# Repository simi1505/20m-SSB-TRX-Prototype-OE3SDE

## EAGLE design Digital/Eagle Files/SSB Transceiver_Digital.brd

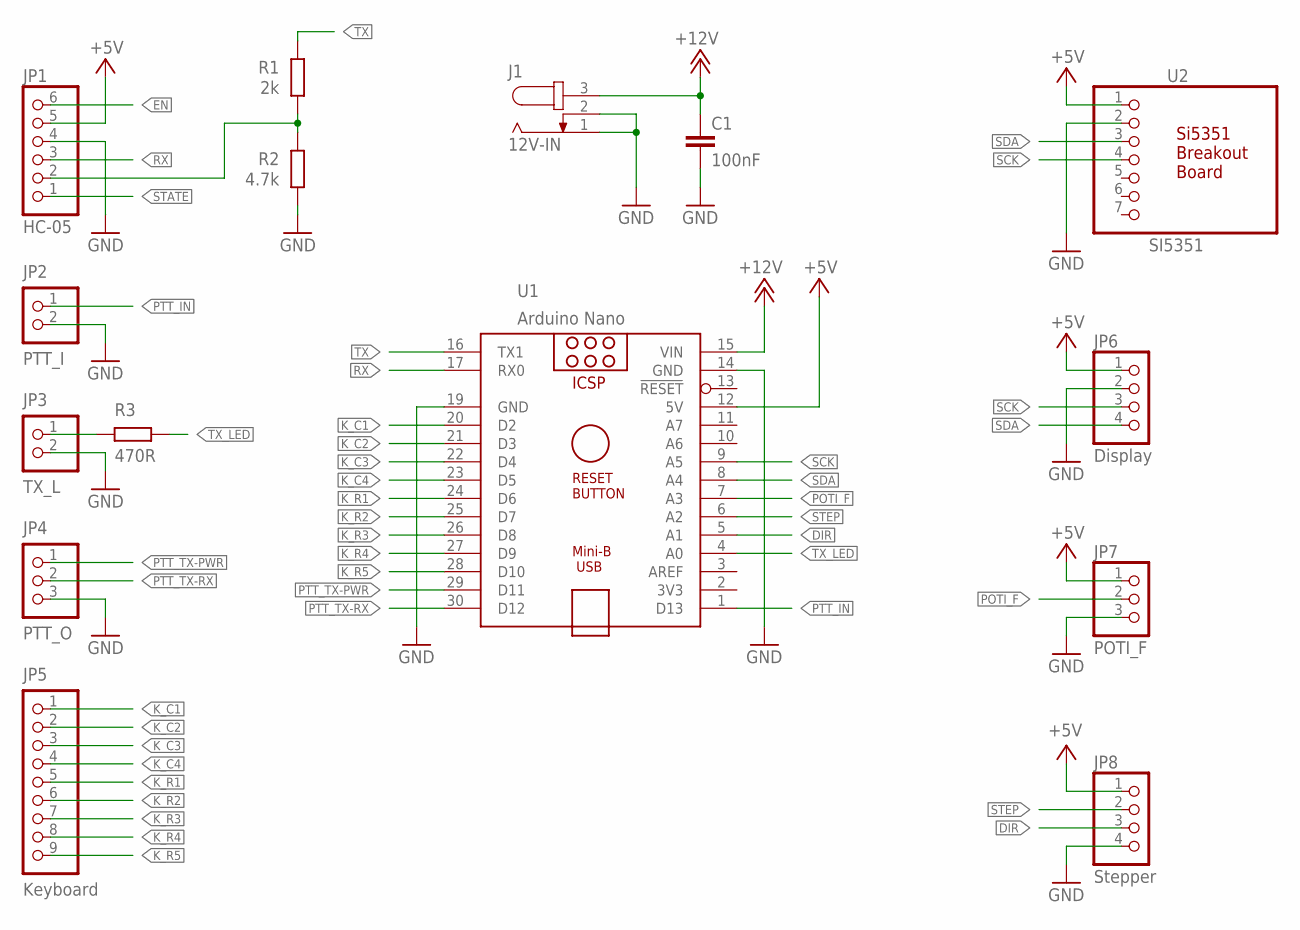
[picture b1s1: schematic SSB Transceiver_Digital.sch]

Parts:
C1: 100nF; C0805K
J1: 12V-IN; SPC4078
JP1: HC-05; 1X06
JP2: PTT_I; 1X02
JP3: TX_L; 1X02
JP4: PTT_O; 1X03
JP5: Keyboard; 1X09
JP6: Display; 1X04
JP7: POTI_F; 1X03
JP8: Stepper; 1X04
R1: 2k; R0805
R2: 4.7k; R0805
R3: 470R; R0805
U1: Arduino Nano; ARDUINO_NANO
U2: SI5351; 1X07

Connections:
+5V: JP1.5, JP6.1, JP7.1, JP8.1, U1.12 (5V), U2.1
+12V: C1.1, J1.3, U1.15 (VIN)
DIR: JP8.3, U1.5 (A1)
EN: JP1.6
GND: C1.2, J1.1, J1.2, JP1.4, JP2.2, JP3.2, JP4.3, JP6.2, JP7.3, JP8.4, R2.1, U1.14 (GND), U1.19 (GND), U2.2
K_C1: JP5.1, U1.20 (D2)
K_C2: JP5.2, U1.21 (D3)
K_C3: JP5.3, U1.22 (D4)
K_C4: JP5.4, U1.23 (D5)
K_R1: JP5.5, U1.24 (D6)
K_R2: JP5.6, U1.25 (D7)
K_R3: JP5.7, U1.26 (D8)
K_R4: JP5.8, U1.27 (D9)
K_R5: JP5.9, U1.28 (D10)
unnamed: JP3.1, R3.2
unnamed: JP1.2, R1.1, R2.2
POTI_F: JP7.2, U1.7 (A3)
PTT_IN: JP2.1, U1.1 (D13)
PTT_TX-PWR: JP4.1, U1.29 (D11)
PTT_TX-RX: JP4.2, U1.30 (D12)
RX: JP1.3, U1.17 (RX0)
SCK: JP6.3, U1.9 (A5), U2.4
SDA: JP6.4, U1.8 (A4), U2.3
STATE: JP1.1
STEP: JP8.2, U1.6 (A2)
TX: R1.2, U1.16 (TX1)
TX_LED: R3.1, U1.4 (A0)

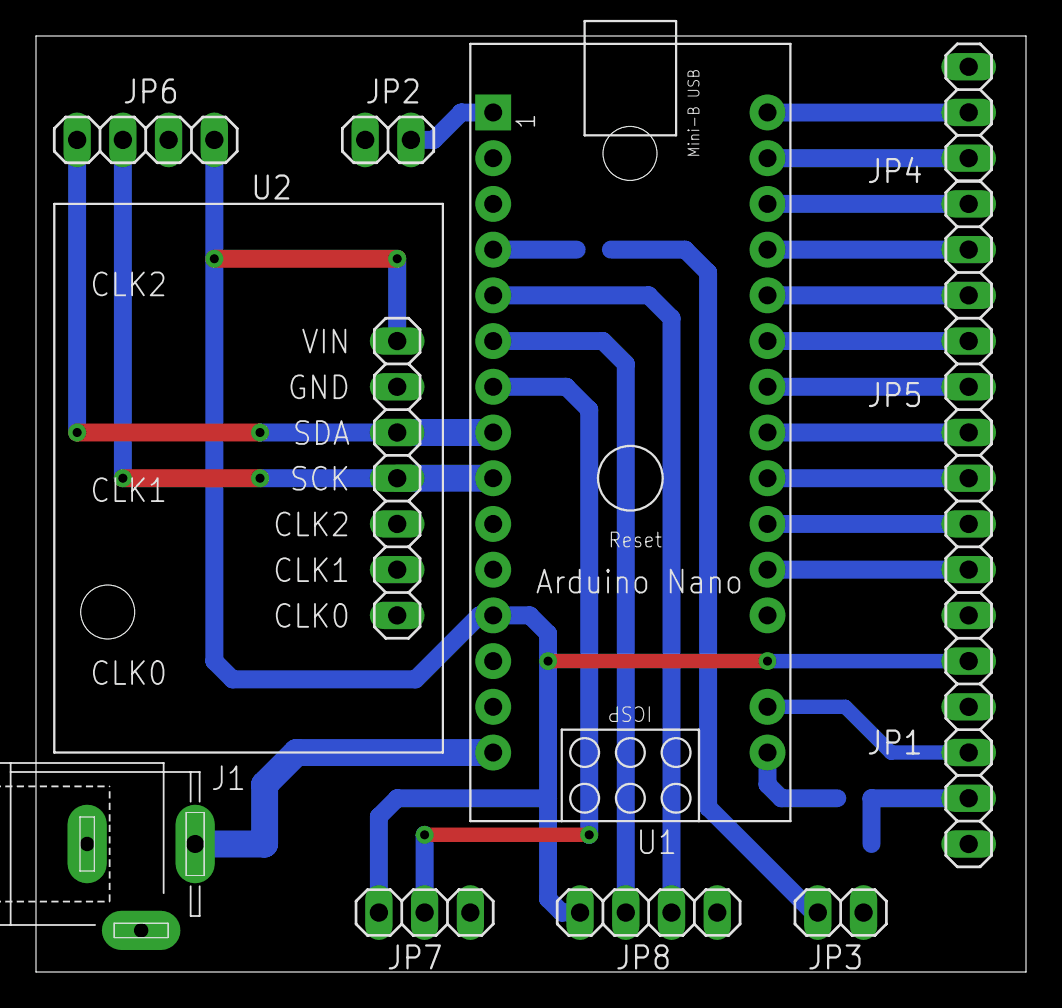
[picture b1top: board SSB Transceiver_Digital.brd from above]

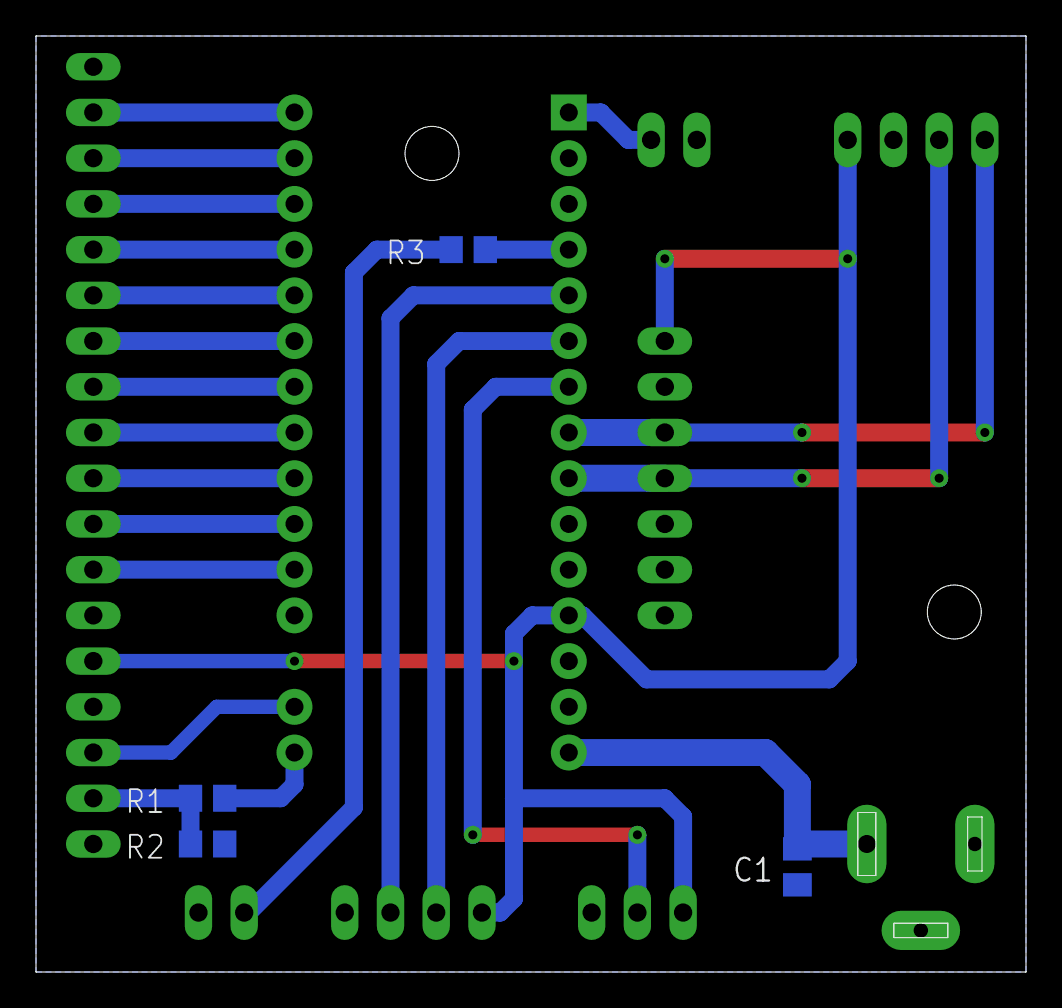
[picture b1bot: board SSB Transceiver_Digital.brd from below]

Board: 2 copper layers, 55.0 x 52.0 mm, 15 parts (4 on the bottom side), 25 nets.

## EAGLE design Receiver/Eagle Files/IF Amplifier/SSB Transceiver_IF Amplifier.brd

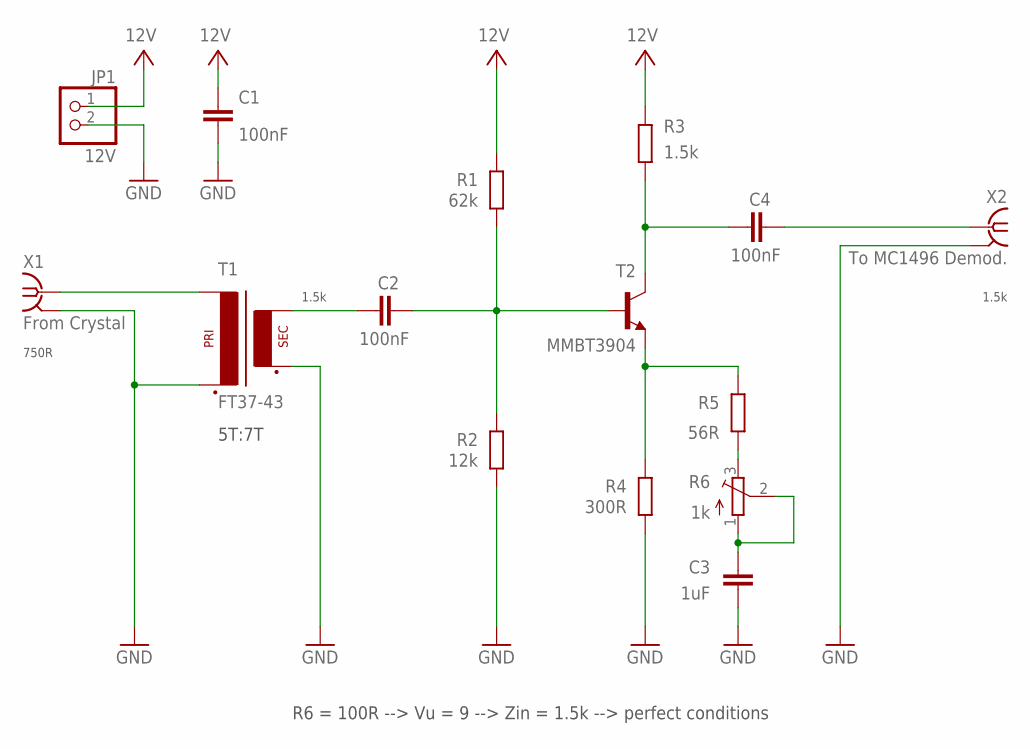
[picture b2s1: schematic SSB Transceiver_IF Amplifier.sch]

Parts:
C1, C2, C4: 100nF; C0805
C3: 1uF; C0805
JP1: 12V; 1X02
R1: 62k; R0805
R2: 12k; R0805
R3: 1.5k; R0805
R4: 300R; R0805
R5: 56R; R0805
R6: 1k; 3223G
T1: FT37-43; FT37-43SMD
T2: MMBT3904; SOT23-BEC
X1: From Crystal; J502-ND-142-0711-821/826
X2: To MC1496 Demod.; J502-ND-142-0711-821/826

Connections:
GND: C1.1, C3.1, JP1.2, R2.2, R4.2, T1.P$2 (P2), T1.S$2 (S2), X1.G@1 (2), X1.G@2 (2), X1.G@3 (2), X1.G@4 (2), X2.G@1 (2), X2.G@2 (2), X2.G@3 (2), X2.G@4 (2)
unnamed: R4.1, R5.1, T2.E
unnamed: C3.2, R6.1 (A), R6.2 (S)
unnamed: C4.1, R3.2, T2.C
unnamed: T1.P$1 (P1), X1.1
unnamed: C2.2, R1.2, R2.1, T2.B
unnamed: C4.2, X2.1
unnamed: C2.1, T1.S$1 (S1)
unnamed: R5.2, R6.3 (E)
VCC: C1.2, JP1.1, R1.1, R3.1

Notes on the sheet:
750R
1.5k
5T:7T
R6 = 100R --> Vu = 9 --> Zin = 1.5k --> perfect conditions

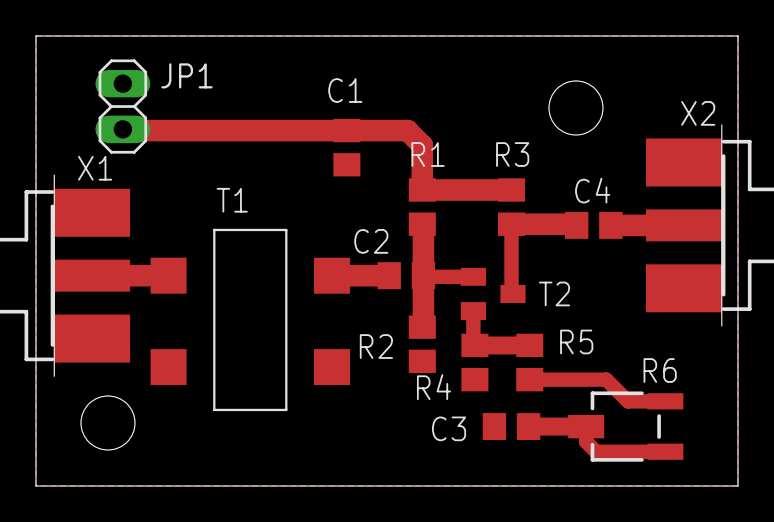
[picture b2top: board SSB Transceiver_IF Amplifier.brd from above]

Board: 2 copper layers, 39.0 x 25.0 mm, 15 parts (0 on the bottom side), 10 nets.

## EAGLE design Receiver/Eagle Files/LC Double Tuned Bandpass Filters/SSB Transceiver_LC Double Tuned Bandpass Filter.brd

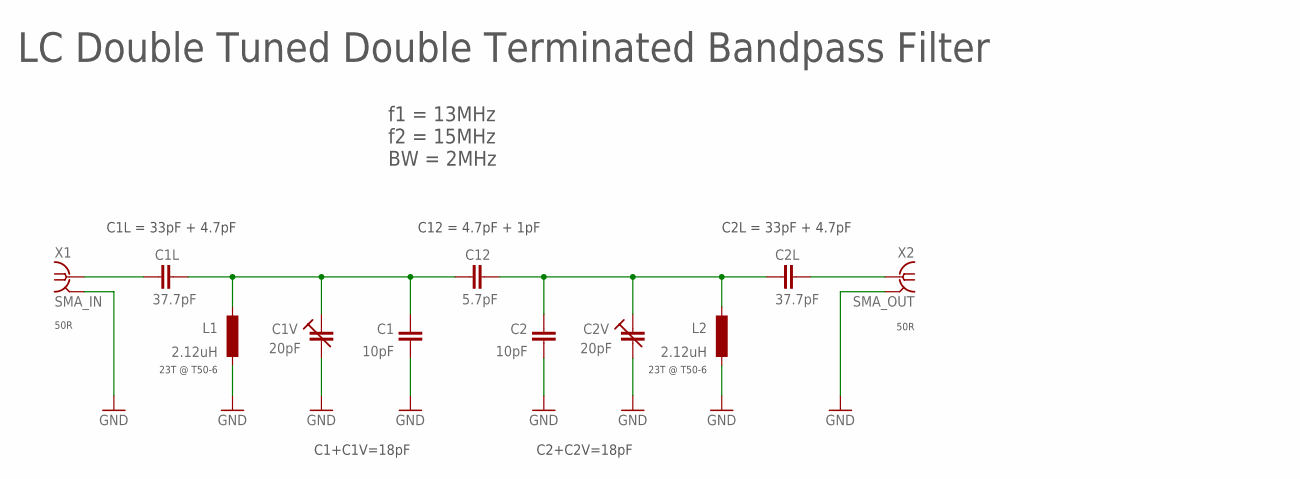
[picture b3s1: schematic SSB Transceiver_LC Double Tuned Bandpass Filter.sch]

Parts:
C1, C2: 10pF; C0805
C1L, C2L: 37.7pF; C0805
C1V, C2V: 20pF; VARIABLECAP-SMD
C12: 5.7pF; C0805
L1, L2: 2.12uH; T50-6SMD
X1: SMA_IN; J502-ND-142-0711-821/826
X2: SMA_OUT; J502-ND-142-0711-821/826

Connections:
GND: C1.1, C1V.P$2 (A), C2.1, C2V.P$2 (A), L1.P$2 (2), L2.P$2 (2), X1.G@1 (2), X1.G@2 (2), X1.G@3 (2), X1.G@4 (2), X2.G@1 (2), X2.G@2 (2), X2.G@3 (2), X2.G@4 (2)
unnamed: C1.2, C1L.2, C1V.P$1 (E), C12.1, L1.P$1 (1)
unnamed: C2.2, C2L.2, C2V.P$1 (E), C12.2, L2.P$1 (1)
unnamed: C2L.1, X2.1
unnamed: C1L.1, X1.1

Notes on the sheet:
50R
C1+C1V=18pF
C2+C2V=18pF
23T @ T50-6
f1 = 13MHz f2 = 15MHz BW = 2MHz
LC Double Tuned Double Terminated Bandpass Filter
C12 = 4.7pF + 1pF
C1L = 33pF + 4.7pF
C2L = 33pF + 4.7pF

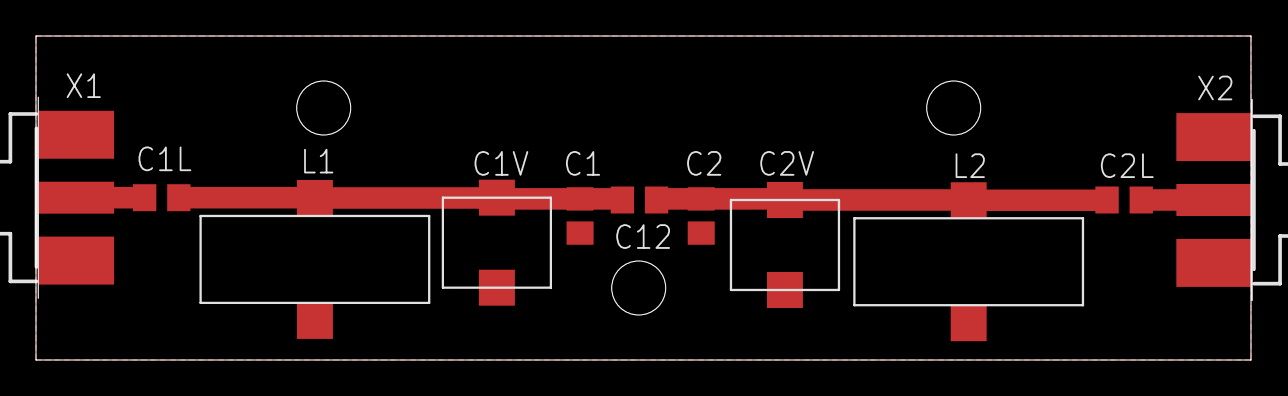
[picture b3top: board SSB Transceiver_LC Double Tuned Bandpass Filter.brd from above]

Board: 2 copper layers, 67.5 x 18.0 mm, 11 parts (0 on the bottom side), 5 nets.

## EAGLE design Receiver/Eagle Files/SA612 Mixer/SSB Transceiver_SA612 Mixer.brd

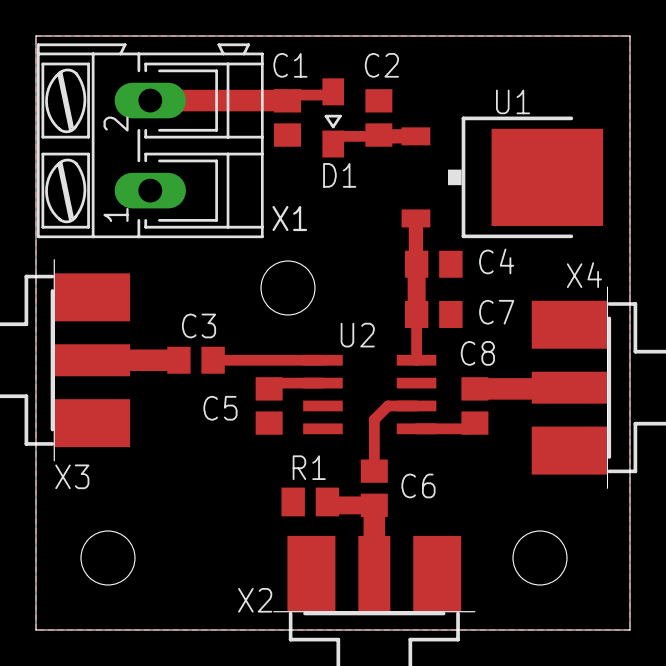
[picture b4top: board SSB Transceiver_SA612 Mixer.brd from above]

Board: 2 copper layers, 33.0 x 33.0 mm, 16 parts (0 on the bottom side), 11 nets.

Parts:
C1, C4, C5, C7, C8: 100nF; C0805
C2: 330nF; C0805
C3: 1nF; C0805
C6: 10nF; C0805
D1: 1N4148; SOD323-W
R1: 51R; M0805
U1: 7805DT; TO252
U2: SA612AD; SO08
X1: 12V; AK300/2
X2: OSC. IN/OUT; J502-ND-142-0711-821/826
X3: IF IN/OUT; J502-ND-142-0711-821/826
X4: RF IN/OUT; J502-ND-142-0711-821/826

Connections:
+5V: C4.2, C7.2, U1.2, U2.8
+24V: C1.2, D1.A, X1.2
GND: C1.1, C2.1, C4.1, C5.1, C7.1, R1.1, U1.3, U2.3, X1.1, X2.G@1, X2.G@2, X2.G@3, X2.G@4, X3.G@1, X3.G@2, X3.G@3, X3.G@4, X4.G@1, X4.G@2, X4.G@3, X4.G@4
unnamed: C6.2, R1.2, X2.1
unnamed: C8.1, X4.1
unnamed: C5.2, U2.2
unnamed: C3.2, X3.1
unnamed: C3.1, U2.1
unnamed: C6.1, U2.6
unnamed: C8.2, U2.5
unnamed: C2.2, D1.C, U1.1

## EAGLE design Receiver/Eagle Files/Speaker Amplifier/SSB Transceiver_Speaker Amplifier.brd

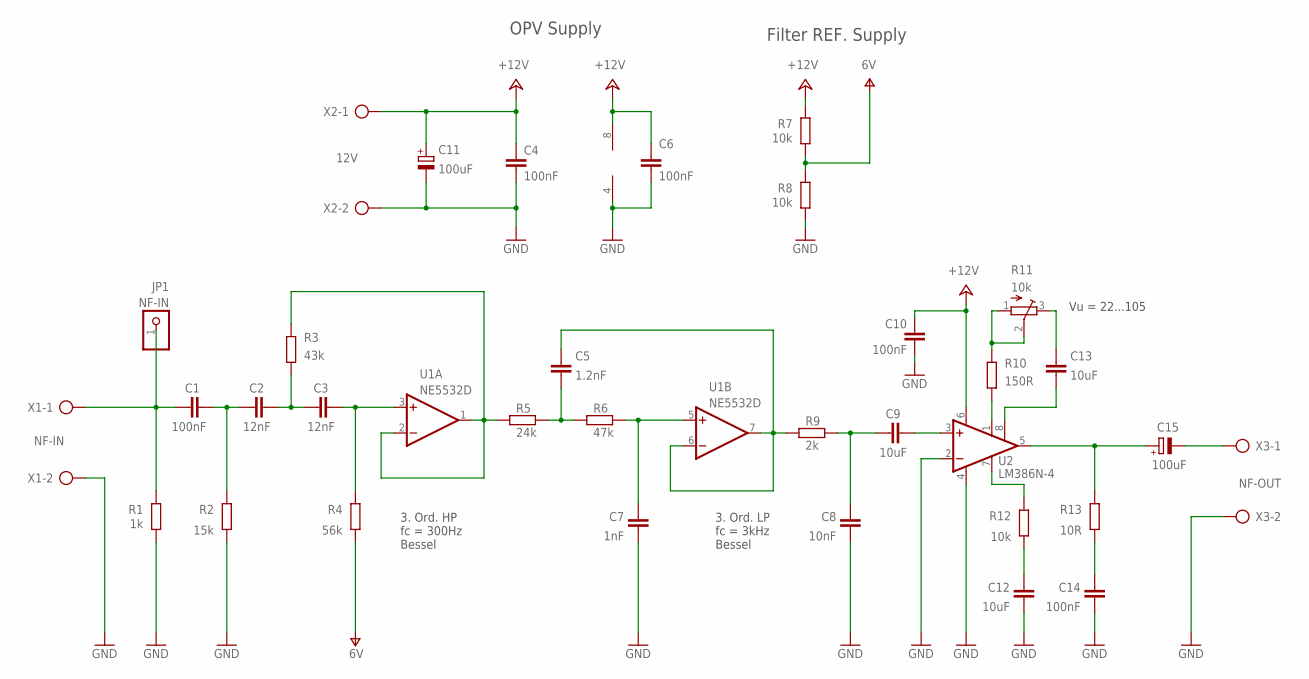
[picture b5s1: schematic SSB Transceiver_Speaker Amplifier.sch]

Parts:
C1, C4, C6, C10, C14: 100nF; C0805
C2, C3: 12nF; C0805
C5: 1.2nF; C0805
C7: 1nF; C0805
C8: 10nF; C0805
C9, C12, C13: 10uF; C0805
C11, C15: 100uF; E2,5-6
JP1: NF-IN; 1X01
R1: 1k; R0805
R2: 15k; R0805
R3: 43k; R0805
R4: 56k; R0805
R5: 24k; R0805
R6: 47k; R0805
R7, R8, R12: 10k; R0805
R9: 2k; R0805
R10: 150R; R0805
R11: 10k; 3223G
R13: 10R; R0805
U1: NE5532D; SO08
U2: LM386N-4; DIL08
X1: NF-IN; AK300/2
X2: 12V; AK300/2
X3: NF-OUT; AK300/2

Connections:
+24V: C4.2, C6.2, C10.2, C11.+, R7.1, U1.8 (V+), U2.6 (VS), X2.1
GND: C4.1, C6.1, C7.1, C8.1, C10.1, C11.-, C12.1, C14.1, R1.2, R2.2, R8.2, U1.4 (V-), U2.2 (-IN), U2.4 (GND), X1.2, X2.2, X3.2
unnamed: C9.2, U2.3 (+IN)
unnamed: R12.1, U2.7 (BYPASS)
unnamed: C12.2, R12.2
unnamed: C1.1, JP1.1, R1.1, X1.1
unnamed: C15.+, R13.1, U2.5 (OUT)
unnamed: C14.2, R13.2
unnamed: R10.2, U2.1 (GAIN)
unnamed: C1.2, C2.1, R2.1
unnamed: C13.2, R11.3 (E)
unnamed: C15.-, X3.1
unnamed: C13.1, U2.8 (GAIN)
unnamed: R3.1, R5.2, U1.1 (OUT), U1.2 (-IN)
unnamed: C2.2, C3.1, R3.2
unnamed: C3.2, R4.1, U1.3 (+IN)
unnamed: C5.1, R5.1, R6.2
unnamed: C7.2, R6.1, U1.5 (+IN)
unnamed: C5.2, R9.2, U1.6 (-IN), U1.7 (OUT)
unnamed: C8.2, C9.1, R9.1
unnamed: R10.1, R11.1 (A), R11.2 (S)
V+: R4.2, R7.2, R8.1

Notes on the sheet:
OPV Supply
Filter REF. Supply
3. Ord. HP fc = 300Hz Bessel
3. Ord. LP fc = 3kHz Bessel
Vu = 22...105

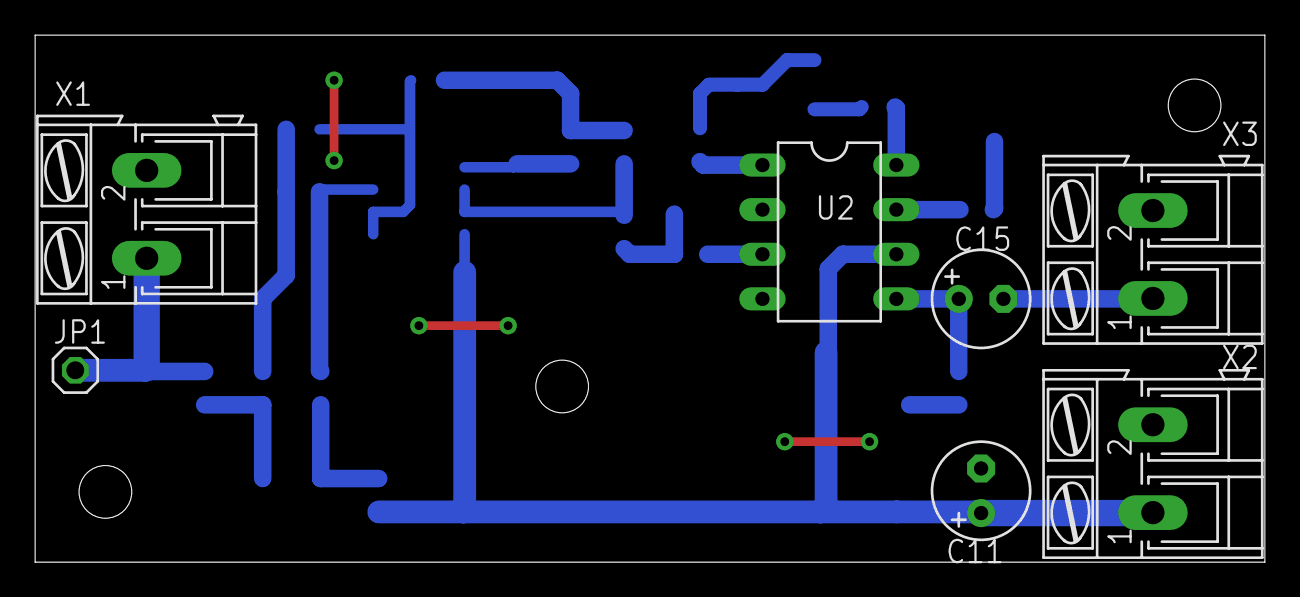
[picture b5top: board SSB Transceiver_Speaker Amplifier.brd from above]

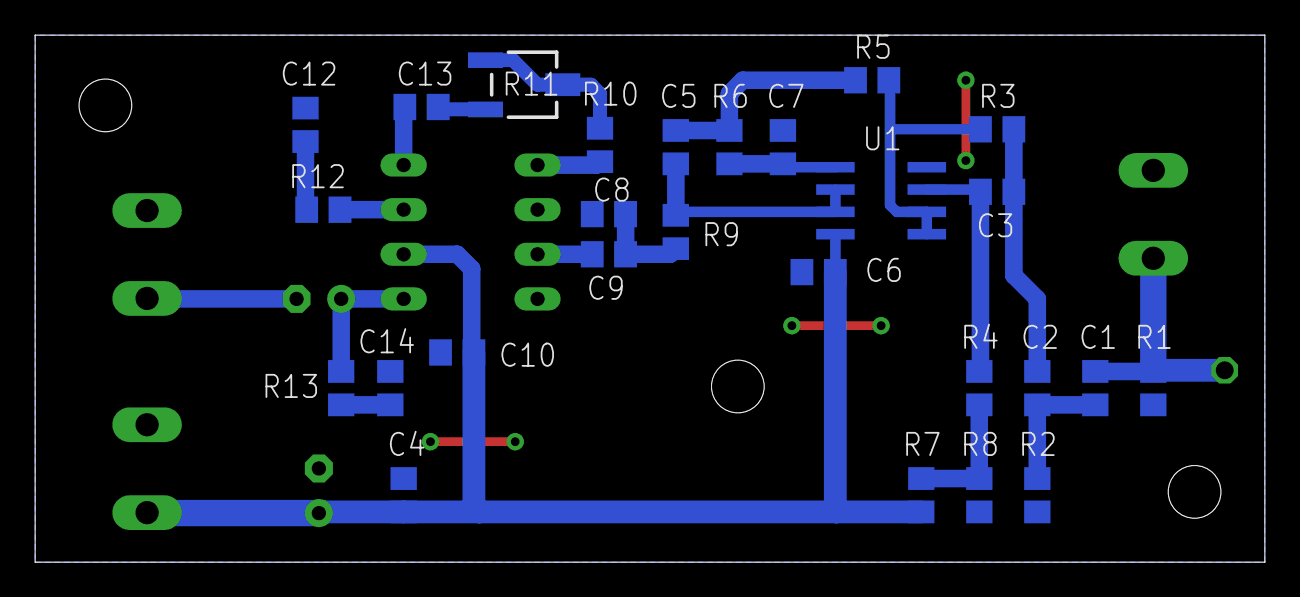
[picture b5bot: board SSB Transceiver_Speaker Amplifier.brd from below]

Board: 2 copper layers, 70.0 x 30.0 mm, 34 parts (27 on the bottom side), 22 nets.

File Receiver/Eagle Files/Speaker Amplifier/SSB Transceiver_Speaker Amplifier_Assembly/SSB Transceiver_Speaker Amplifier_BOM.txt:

Partlist exported from E:/Simon Dorrer/DIY Projekte/Amateurfunkprojekte/SSB Transceiver/Receiver/Eagle Files/Speaker Amplifier/SSB Transceiver_Speaker Amplifier.sch at 11/03/2020 00:20

Qty Value    Device        Package Parts                Description                          MF MPN OC_FARNELL OC_NEWARK POPULARITY SPICEPREFIX
1   1.2nF    C-EUC0805     C0805   C5                   CAPACITOR, European symbol                                       88         C          
5   100nF    C-EUC0805     C0805   C1, C4, C6, C10, C14 CAPACITOR, European symbol                                       88         C          
2   100uF    CPOL-EUE2.5-6 E2,5-6  C11, C15             POLARIZED CAPACITOR, European symbol                             26         C          
1   10R      R-EU_R0805    R0805   R13                  RESISTOR, European symbol                                        86         R          
3   10k      R-EU_R0805    R0805   R7, R8, R12          RESISTOR, European symbol                                        86         R          
1   10k      TRIM_EU-3223G 3223G   R11                  POTENTIOMETER                                                                          
1   10nF     C-EUC0805     C0805   C8                   CAPACITOR, European symbol                                       88         C          
3   10uF     C-EUC0805     C0805   C9, C12, C13         CAPACITOR, European symbol                                       88         C          
1   12V      AK300/2       AK300/2 X2                   CONNECTOR                                   unknown    unknown                         
2   12nF     C-EUC0805     C0805   C2, C3               CAPACITOR, European symbol                                       88         C          
1   150R     R-EU_R0805    R0805   R10                  RESISTOR, European symbol                                        86         R          
1   15k      R-EU_R0805    R0805   R2                   RESISTOR, European symbol                                        86         R          
1   1k       R-EU_R0805    R0805   R1                   RESISTOR, European symbol                                        86         R          
1   1nF      C-EUC0805     C0805   C7                   CAPACITOR, European symbol                                       88         C          
1   24k      R-EU_R0805    R0805   R5                   RESISTOR, European symbol                                        86         R          
1   2k       R-EU_R0805    R0805   R9                   RESISTOR, European symbol                                        86         R          
1   43k      R-EU_R0805    R0805   R3                   RESISTOR, European symbol                                        86         R          
1   47k      R-EU_R0805    R0805   R6                   RESISTOR, European symbol                                        86         R          
1   56k      R-EU_R0805    R0805   R4                   RESISTOR, European symbol                                        86         R          
1   LM386N-4 LM386N-4      DIL08   U2                   Low Voltage Audio Power Amplifier                                                      
1   NE5532D  NE5532D       SO08    U1                   AUDIO AMPLIFIER                                                                        
1   NF-IN    AK300/2       AK300/2 X1                   CONNECTOR                                   unknown    unknown                         
1   NF-IN    PINHD-1X1     1X01    JP1                  PIN HEADER                                                                             
1   NF-OUT   AK300/2       AK300/2 X3                   CONNECTOR                                   unknown    unknown

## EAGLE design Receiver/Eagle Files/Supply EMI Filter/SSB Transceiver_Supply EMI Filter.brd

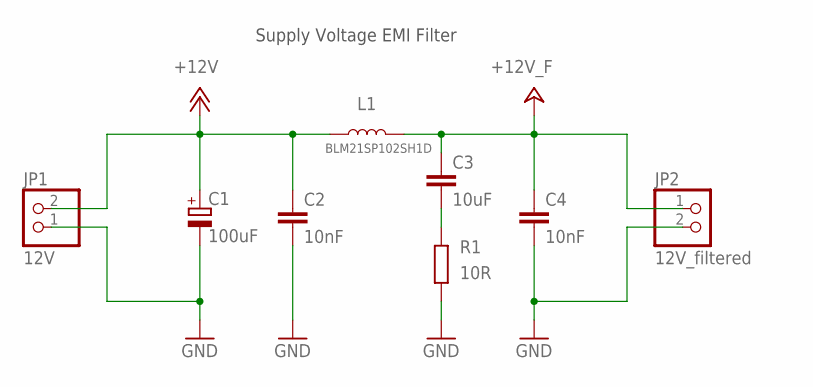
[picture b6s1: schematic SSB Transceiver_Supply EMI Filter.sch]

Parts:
C1: 100uF; E2,5-7
C2, C4: 10nF; C0805
C3: 10uF; C0805
JP1: 12V; 1X02
JP2: 12V_filtered; 1X02
L1: BLM21SP102SH1D; 0805
R1: 10R; R0805

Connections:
+12V: C1.+, C2.1, JP1.2, L1.1
+24V: C3.1, C4.1, JP2.1, L1.2
GND: C1.-, C2.2, C4.2, JP1.1, JP2.2, R1.1
unnamed: C3.2, R1.2

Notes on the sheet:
Supply Voltage EMI Filter

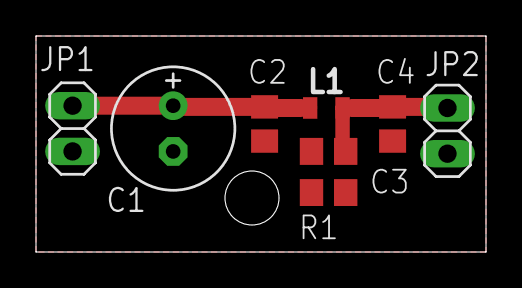
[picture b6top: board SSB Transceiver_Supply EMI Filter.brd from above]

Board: 2 copper layers, 25.0 x 12.0 mm, 8 parts (0 on the bottom side), 4 nets.

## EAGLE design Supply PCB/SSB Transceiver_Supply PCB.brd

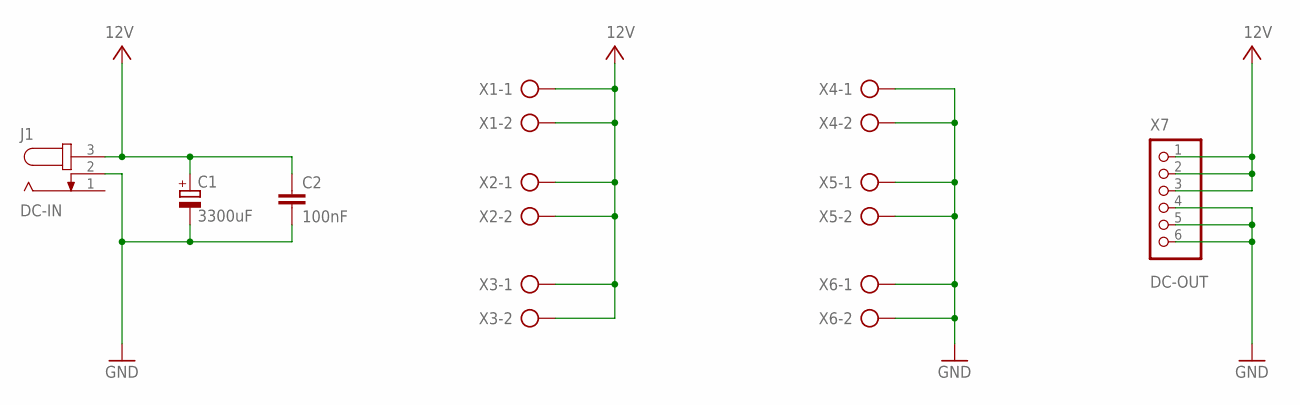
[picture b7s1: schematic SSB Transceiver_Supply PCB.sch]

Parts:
C1: 3300uF; E7,5-16
C2: 100nF; C0805K
J1: DC-IN; SPC4078
X1: 12V; AK300/2
X2, X3, X4, X5, X6: AK300/2
X7: DC-OUT; 1X06

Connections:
GND: C1.-, C2.2, J1.2, X4.1, X4.2, X5.1, X5.2, X6.1, X6.2, X7.4, X7.5, X7.6
VCC: C1.+, C2.1, J1.3, X1.1, X1.2, X2.1, X2.2, X3.1, X3.2, X7.1, X7.2, X7.3

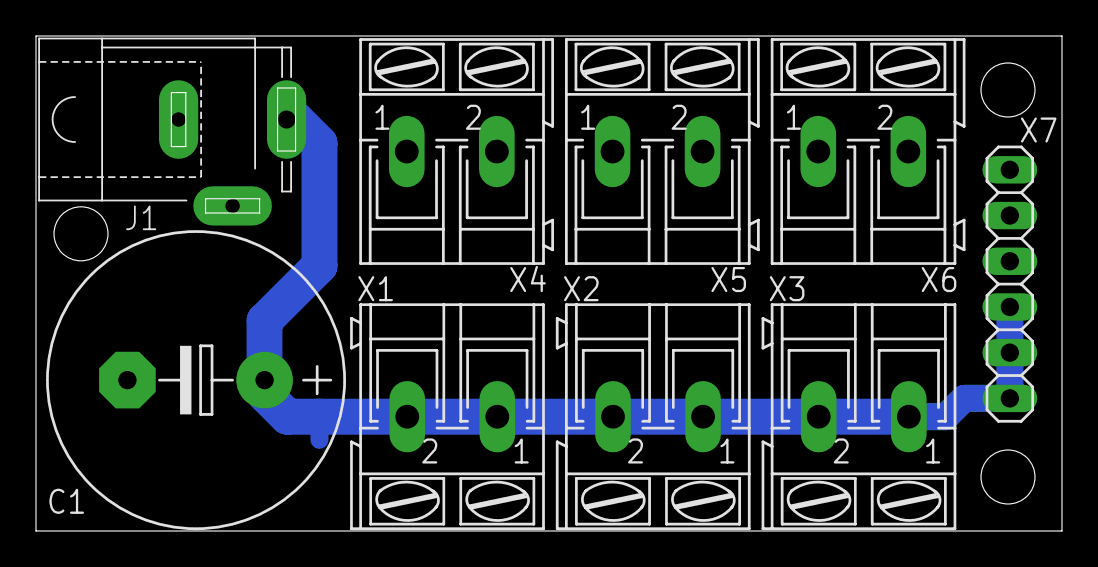
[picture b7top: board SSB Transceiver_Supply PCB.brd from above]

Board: 2 copper layers, 57.0 x 27.5 mm, 10 parts (1 on the bottom side), 2 nets.

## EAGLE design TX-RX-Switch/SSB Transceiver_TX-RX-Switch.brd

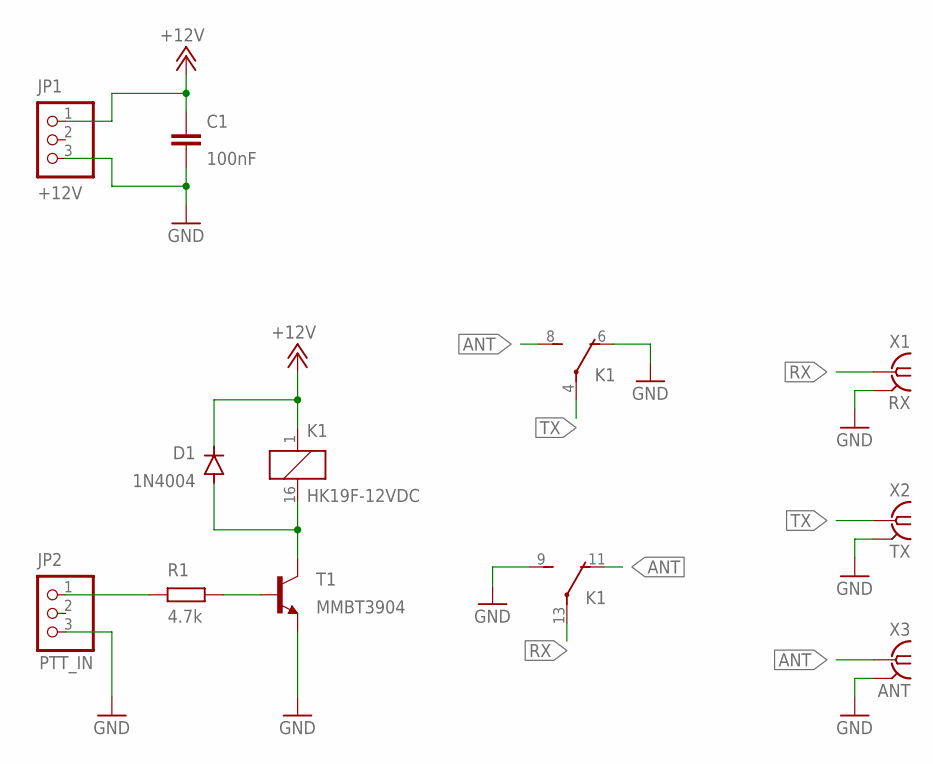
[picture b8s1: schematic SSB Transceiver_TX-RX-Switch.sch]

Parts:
C1: 100nF; C0805K
D1: 1N4004; DO41-10
JP1: +12V; 1X03
JP2: PTT_IN; 1X03
K1: HK19F-12VDC
R1: 4.7k; R0805
T1: MMBT3904; SOT23-BEC
X1: RX; J502-ND-142-0711-821/826_BOTTOM
X2: TX; J502-ND-142-0711-821/826_BOTTOM
X3: ANT; J502-ND-142-0711-821/826_BOTTOM

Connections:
+12V: C1.1, D1.C, JP1.1, K1.1 (A)
ANT: K1.8 (S), K1.11 (O), X3.RF
GND: C1.2, JP1.3, JP2.3, K1.6 (O), K1.9 (S), T1.E, X1.G@1 (GND), X1.G@2 (GND), X2.G@1 (GND), X2.G@2 (GND), X3.G@1 (GND), X3.G@2 (GND)
unnamed: R1.2, T1.B
unnamed: D1.A, K1.16 (B), T1.C
unnamed: JP2.1, R1.1
RX: K1.13, X1.RF
TX: K1.4, X2.RF

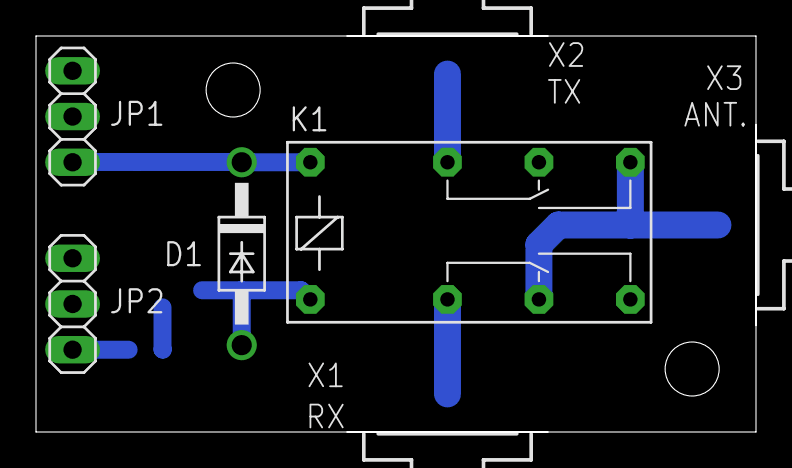
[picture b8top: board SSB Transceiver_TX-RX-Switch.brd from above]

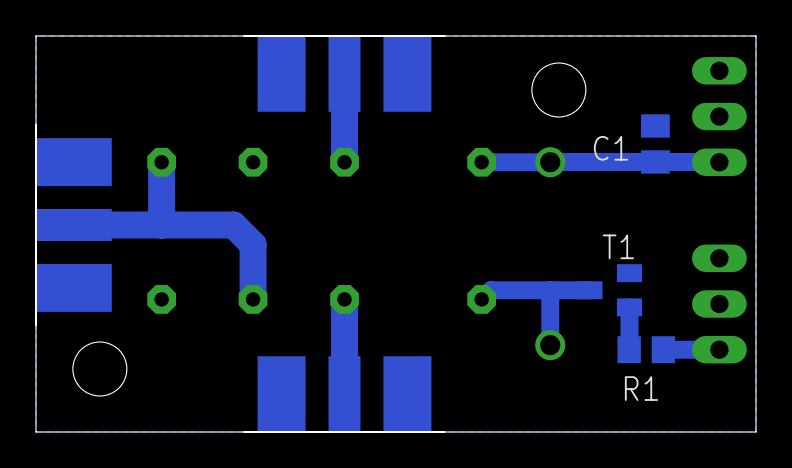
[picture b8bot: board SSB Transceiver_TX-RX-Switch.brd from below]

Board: 2 copper layers, 40.0 x 22.0 mm, 10 parts (3 on the bottom side), 8 nets.

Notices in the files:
parts and their libraries:
SparkFun-Coils: Licensing: Creative Commons ShareAlike 4.0 International - https://creativecommons.org/licenses/by-sa/4.0
